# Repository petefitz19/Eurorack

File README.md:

# Eurorack
Collection of Eurorack Module Hardware and Software

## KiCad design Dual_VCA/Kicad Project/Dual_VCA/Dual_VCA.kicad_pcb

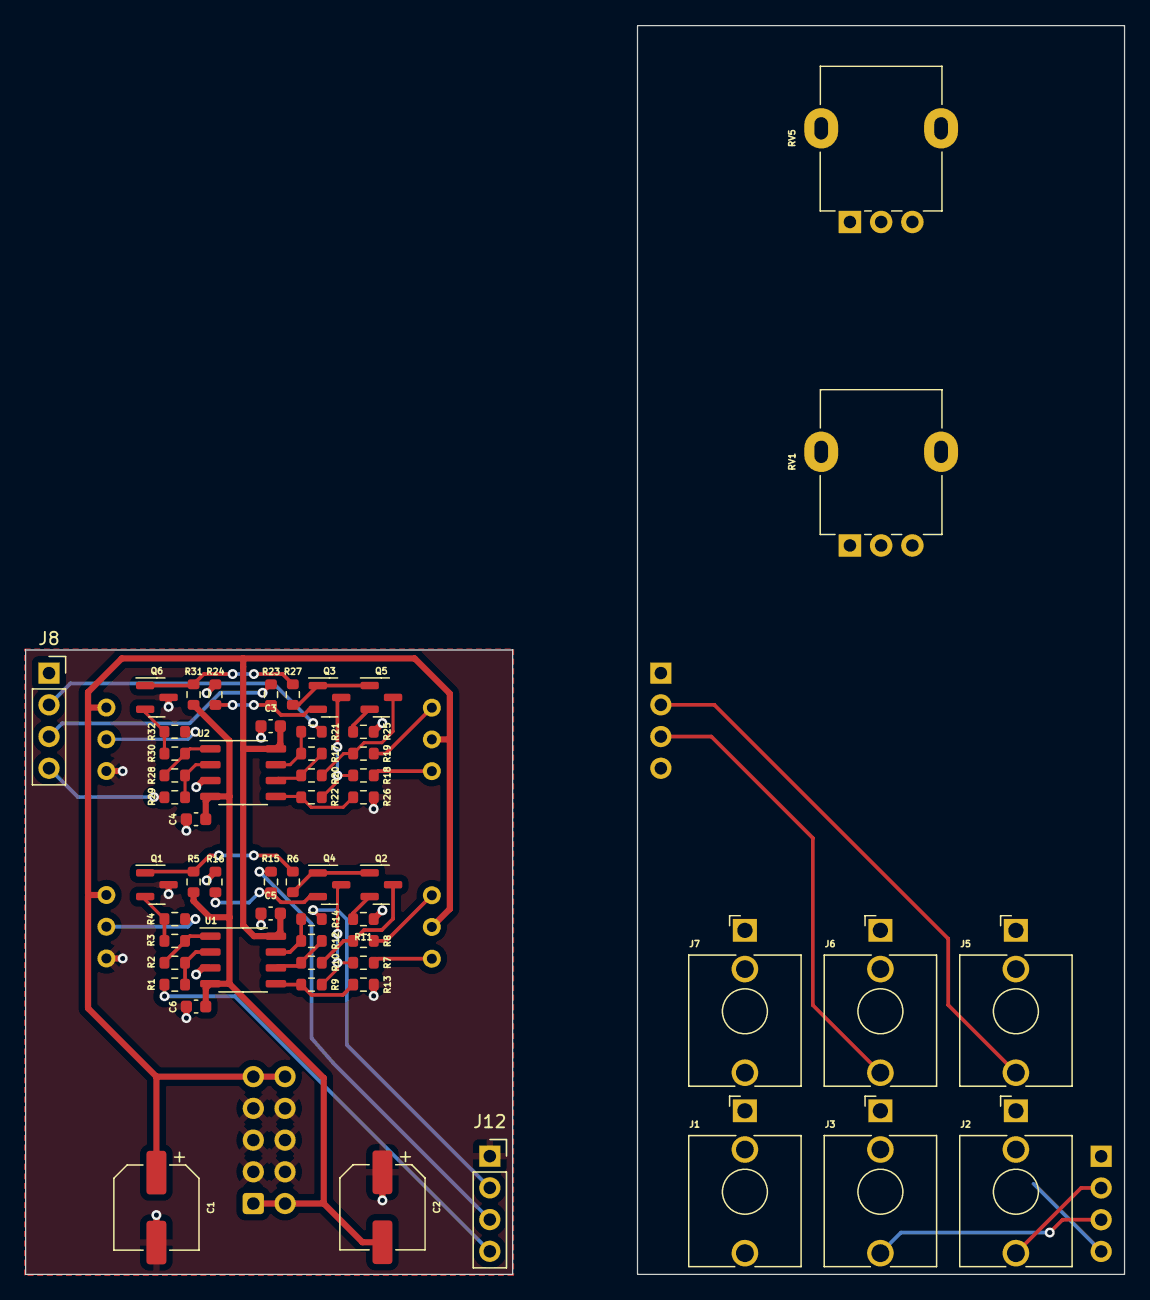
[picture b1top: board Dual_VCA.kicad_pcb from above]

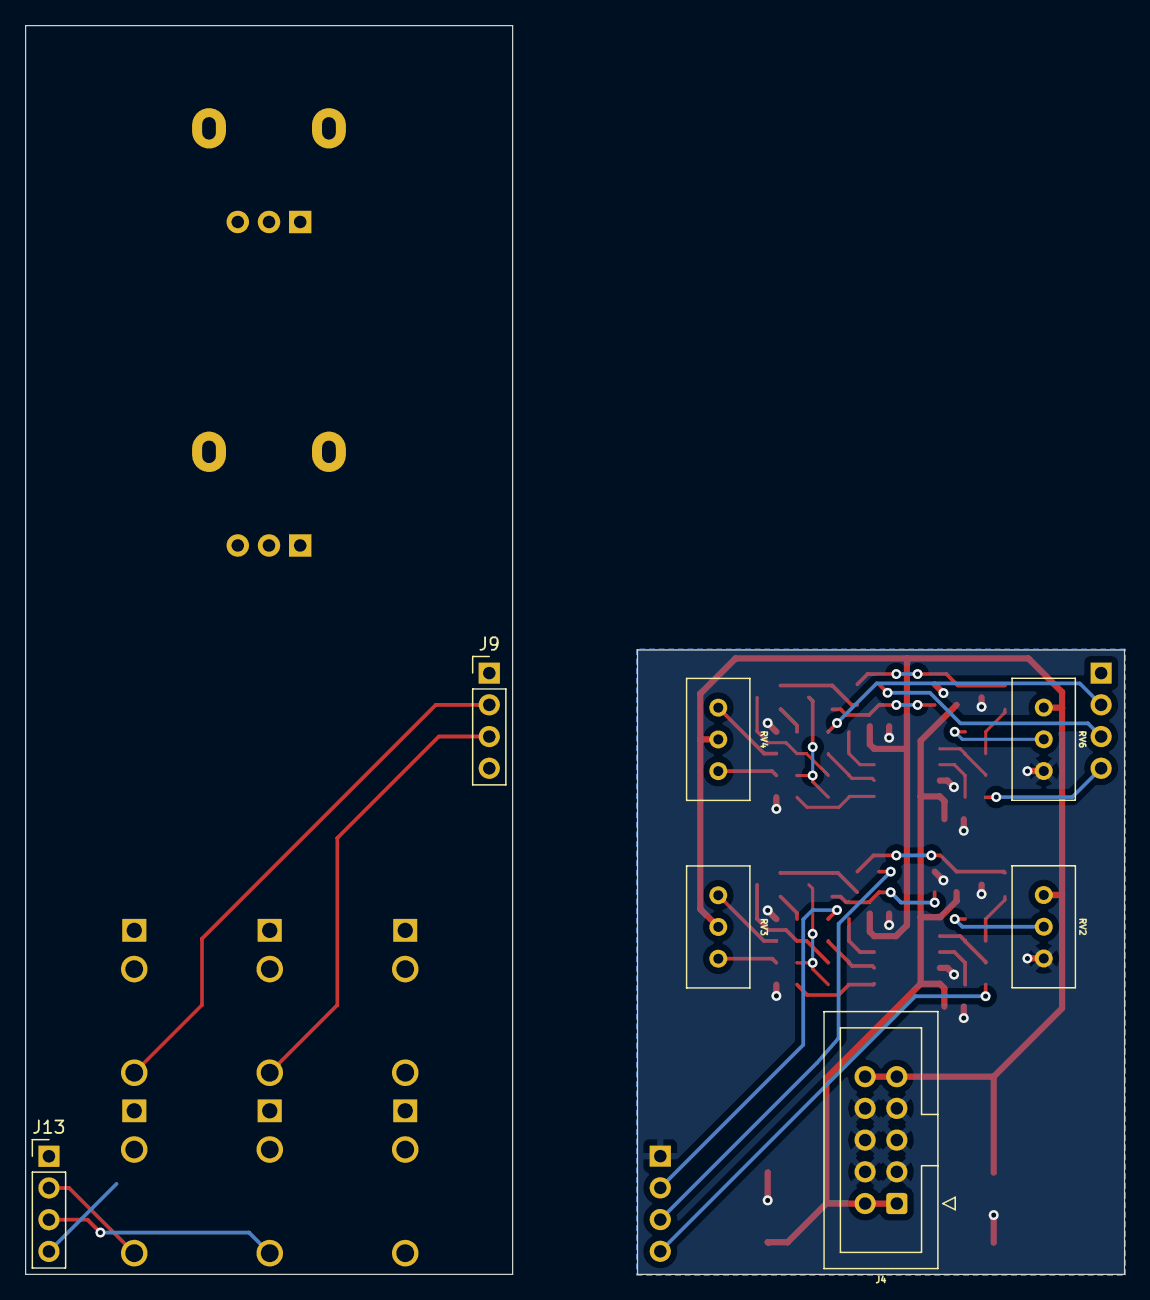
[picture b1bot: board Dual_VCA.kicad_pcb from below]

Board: 2 copper layers, 88.0 x 100.0 mm, 63 parts (7 on the bottom side), 47 nets.

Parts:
C1, C2: 10uF; CP_Elec_6.3x5.4
C3, C4, C5, C6: 100nF; C_0603_1608Metric
J1, J7: CV_IN; Jack_3.5mm_QingPu_WQP-PJ398SM_Vertical_CircularHoles
J2, J5: AUDIO_OUT; Jack_3.5mm_QingPu_WQP-PJ398SM_Vertical_CircularHoles
J3, J6: AUDIO_IN; Jack_3.5mm_QingPu_WQP-PJ398SM_Vertical_CircularHoles
J4: PWR; IDC-Header_2x05_P2.54mm_Vertical
J8: Conn_2A; PinSocket_1x04_P2.54mm_Vertical
J9: Conn_2B; PinHeader_1x04_P2.54mm_Vertical
J12: Conn_1A; PinSocket_1x04_P2.54mm_Vertical
J13: Conn_1B; PinHeader_1x04_P2.54mm_Vertical
Q1, Q2, Q3, Q4, Q5, Q6: 2N3904; SOT-23
R1, R2, R28, R29: 100k; R_0603_1608Metric
R3, R4, R5, R30, R31, R32: 10k; R_0603_1608Metric
R6, R27: 33k; R_0603_1608Metric
R7, R8, R9, R10, R18, R19, R20, R22: 15k; R_0603_1608Metric
R11, R14, R16, R21, R24, R25: 1K; R_0603_1608Metric
R12, R13, R17, R26: 150k; R_0603_1608Metric
R15, R23: 200k; R_0603_1608Metric
RV1, RV5: 100k; Potentiometer_Alpha_RD901F-40-00D_Single_Vertical
RV2, RV6: 10k; Potentiometer_Bourns_3296W_Vertical
RV3, RV4: 5k; Potentiometer_Bourns_3296W_Vertical
U1, U2: TL072; SOP-8_3.9x4.9mm_P1.27mm

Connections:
+12V: C1.1, C3.2, C5.2, J4.9, J4.10, RV2.3, RV3.2, RV4.2, RV6.3, U1.8 (V+), U2.8 (V+)
-12V: C2.2, C4.2, C6.2, J4.1, J4.2, R5.2, R31.2, U1.4 (V-), U2.4 (V-)
/cv1_a: J12.4, R1.2
/cv1_b: J13.4, RV1.2
/cv2_a: J8.4, R29.2
/cv2_b: J9.4, RV5.2
/in1_a: J12.3, R15.1
/in1_b: J3.T, J13.3
/in2_a: J8.3, R23.1
/in2_b: J6.T, J9.3
/out1_a: J12.2, R14.1
/out1_b: J2.T, J13.2
/out2_a: J8.2, R21.1
/out2_b: J5.T, J9.2
GND: C1.2, C2.1, C3.1, C4.1, C5.1, C6.1, J1.S, J2.S, J3.S, J4.3, J4.4, J4.5, J4.6, J4.7, J4.8, J5.S, J6.S, J7.S, J12.1, J13.1, Q1.3 (C), Q6.3 (C), R11.1, R13.1, R16.1, R24.1, R25.1, R26.1, RV1.1, RV2.1, RV5.1, RV6.1, U1.3 (+), U2.3 (+)
unnamed: J1.T, RV1.3
unnamed: J7.T, RV5.3
unnamed: Q1.2 (B), R3.1, R4.1
unnamed: Q1.1 (E), R5.1, R6.2
unnamed: Q2.2 (B), R11.2
unnamed: Q2.3 (C), R8.2, R10.1
unnamed: Q2.1 (E), Q4.1 (E), R6.1
unnamed: Q3.2 (B), R23.2, R24.2
unnamed: Q3.3 (C), R18.2, R22.1
unnamed: Q3.1 (E), Q5.1 (E), R27.1
unnamed: Q4.2 (B), R15.2, R16.2
unnamed: Q4.3 (C), R7.2, R9.1
unnamed: Q5.2 (B), R25.2
unnamed: Q5.3 (C), R19.2, R20.1
unnamed: Q6.2 (B), R30.1, R32.1
unnamed: Q6.1 (E), R27.2, R31.1
unnamed: R2.1, R3.2, U1.1
unnamed: R4.2, RV2.2
unnamed: R7.1, RV3.1
unnamed: R8.1, RV3.3
unnamed: R12.2, R14.2, U1.7
unnamed: R17.2, R21.2, U2.7
unnamed: R18.1, RV4.1
unnamed: R19.1, RV4.3
unnamed: R28.1, R30.2, U2.1
unnamed: R32.2, RV6.2
unnamed: R1.1, R2.2, U1.2 (-)
unnamed: R9.2, R13.2, U1.5 (+)
unnamed: R10.2, R12.1, U1.6 (-)
unnamed: R28.2, R29.1, U2.2 (-)
unnamed: R22.2, R26.2, U2.5 (+)
unnamed: R17.1, R20.2, U2.6 (-)

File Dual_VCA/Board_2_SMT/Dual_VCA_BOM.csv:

Comment,Designator,Footprint,LCSC Part Number
10uF,"C1,C2",CP_Elec_6.3x5.4,C5221839
100nF Unpolarized capacitor,"C3,C4,C5,C6",C_0603_1608Metric,C1591
"2N3904 0.2A Ic, 40V Vce, Small Signal NPN Transistor, TO-92","Q1,Q2,Q3,Q4,Q5,Q6",SOT-23,C18536
100k Resistor,"R1,R2,R28,R29",R_0603_1608Metric,C25803
10k Resistor,"R3,R4,R5,R30,R31,R32",R_0603_1608Metric,C25804
33k Resistor,"R6,R27",R_0603_1608Metric,C4216
15k Resistor,"R7,R8,R9,R10,R18,R19,R20,R22",R_0603_1608Metric,C22809
1K Resistor,"R11,R14,R16,R21,R24,R25",R_0603_1608Metric,C21190
150k Resistor,"R12,R13,R17,R26",R_0603_1608Metric,C22807
200k Resistor,"R15,R23",R_0603_1608Metric,C25811
"TL072 Dual Low-Noise JFET-Input Operational Amplifiers, DIP-8/SOIC-8","U1,U2",SOP-8_3.9x4.9mm_P1.27mm,C67473

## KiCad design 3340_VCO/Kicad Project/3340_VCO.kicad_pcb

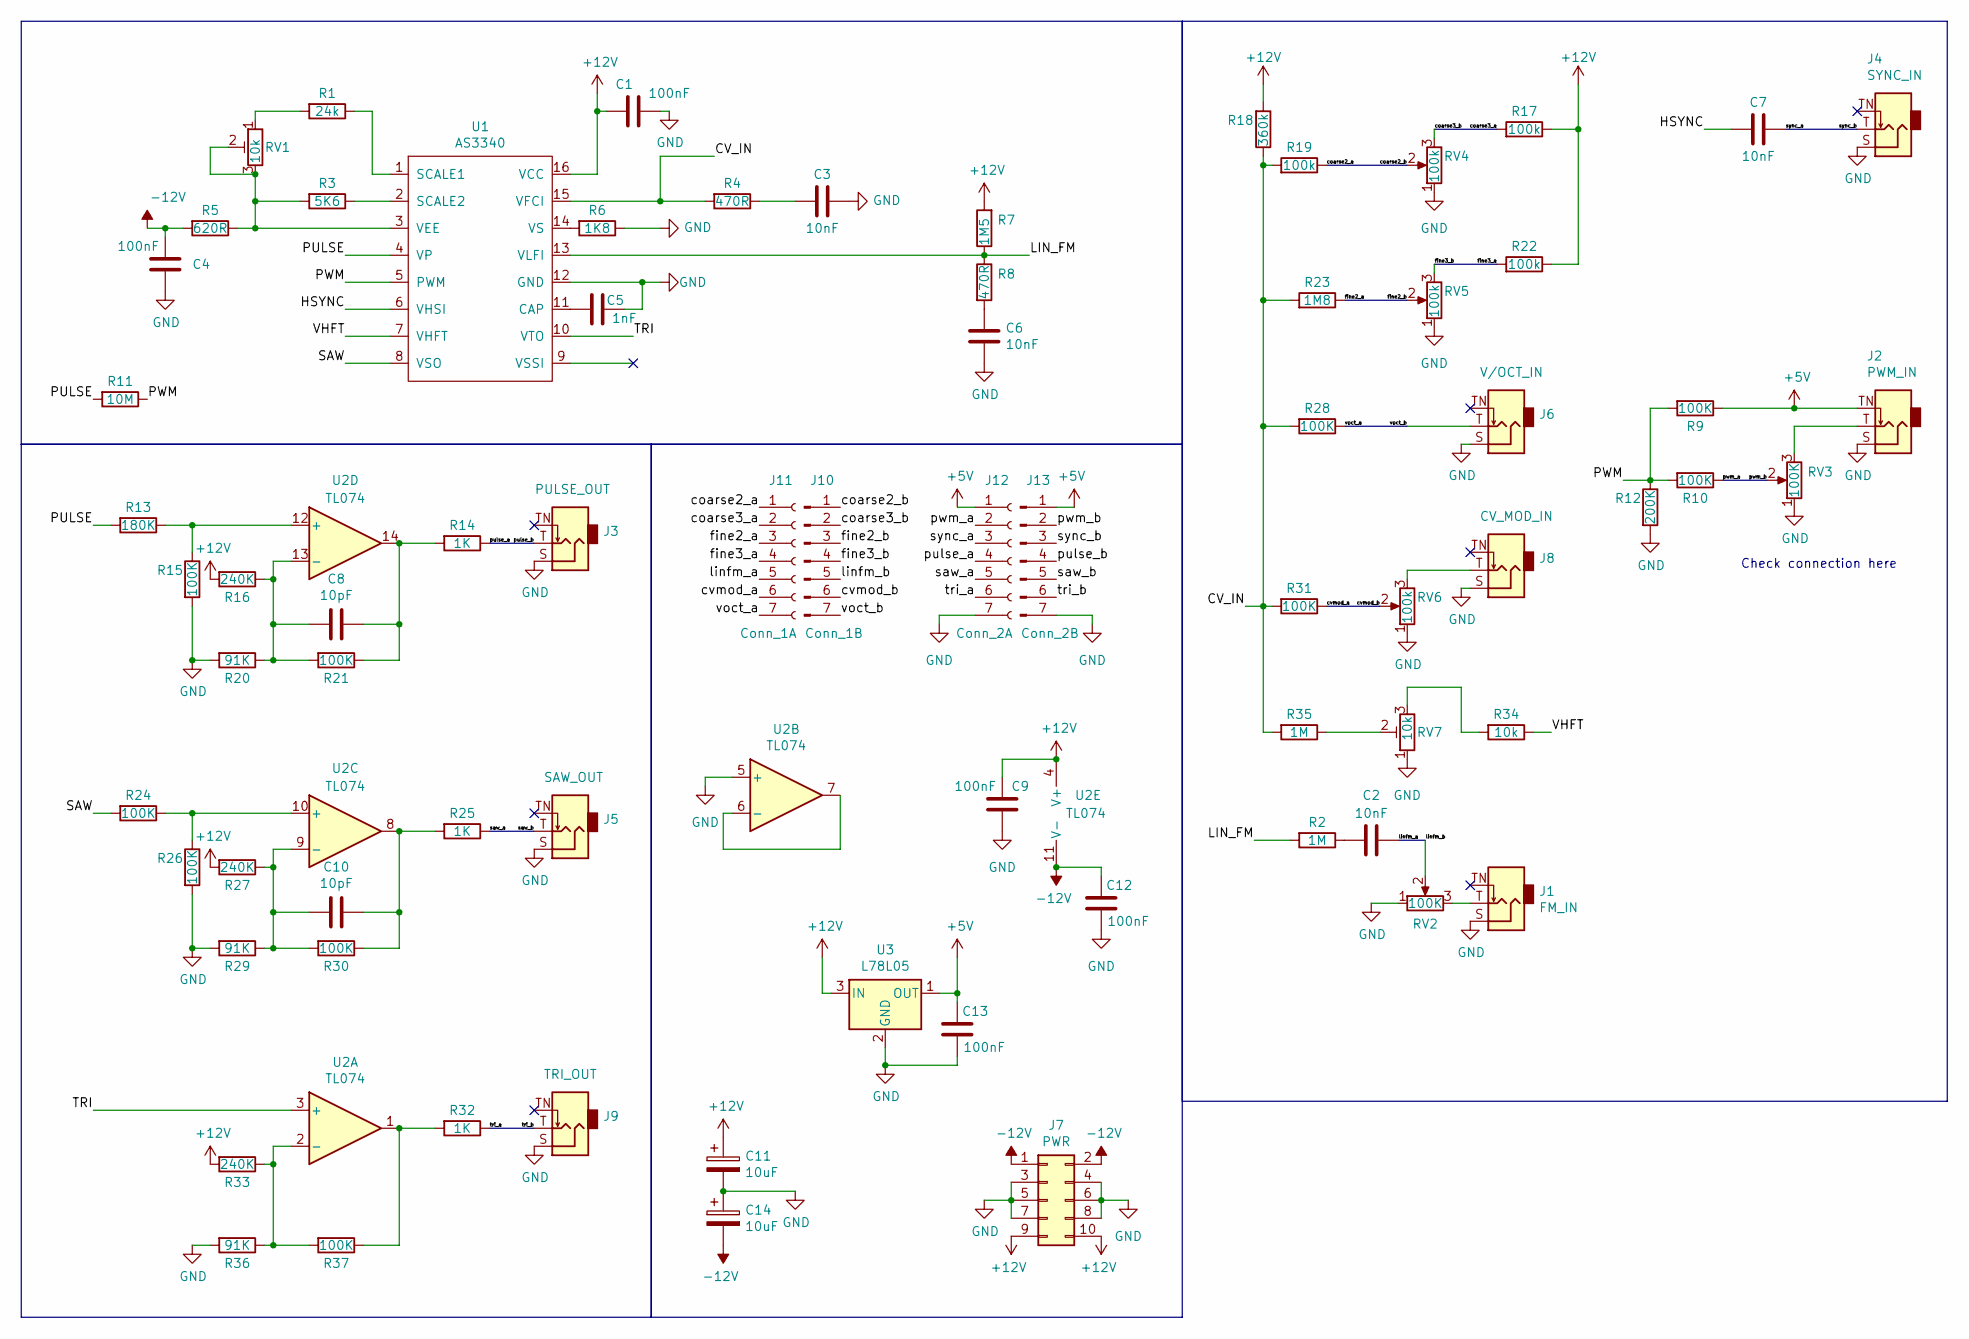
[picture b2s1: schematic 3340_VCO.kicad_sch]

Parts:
C1, C4, C9, C12, C13: 100nF; C_0603_1608Metric; LCSC C1591
C2, C3, C6, C7: 10nF; C_0603_1608Metric; LCSC C100042
C5: 1nF; C_0603_1608Metric; LCSC C178413
C8, C10: 10pF; C_0603_1608Metric; LCSC C91367
C11, C14: 10uF; CP_Elec_6.3x5.4; LCSC C5221839
J1: FM_IN; Jack_3.5mm_QingPu_WQP-PJ398SM_Vertical_CircularHoles
J2: PWM_IN; Jack_3.5mm_QingPu_WQP-PJ398SM_Vertical_CircularHoles
J3: PULSE_OUT; Jack_3.5mm_QingPu_WQP-PJ398SM_Vertical_CircularHoles
J4: SYNC_IN; Jack_3.5mm_QingPu_WQP-PJ398SM_Vertical_CircularHoles
J5: SAW_OUT; Jack_3.5mm_QingPu_WQP-PJ398SM_Vertical_CircularHoles
J6: V/OCT_IN; Jack_3.5mm_QingPu_WQP-PJ398SM_Vertical_CircularHoles
J7: PWR; IDC-Header_2x05_P2.54mm_Vertical
J8: CV_MOD_IN; Jack_3.5mm_QingPu_WQP-PJ398SM_Vertical_CircularHoles
J9: TRI_OUT; Jack_3.5mm_QingPu_WQP-PJ398SM_Vertical_CircularHoles
J10: Conn_1A; PinSocket_1x07_P2.54mm_Vertical
J11: Conn_1B; PinHeader_1x07_P2.54mm_Vertical
J12: Conn_2B; PinHeader_1x07_P2.54mm_Vertical
J13: Conn_2A; PinSocket_1x07_P2.54mm_Vertical
R1: 24k; R_0603_1608Metric; LCSC C23352
R2, R35: 1M; R_0603_1608Metric; LCSC C22935
R3: 5K6; R_0603_1608Metric; LCSC C23189
R4, R8: 470R; R_0603_1608Metric; LCSC C23179
R5: 620R; R_0603_1608Metric; LCSC C23220
R6: 1K8; R_0603_1608Metric; LCSC C4177
R7: 1M5; R_0603_1608Metric; LCSC C4172
R9, R10, R15, R21, R24, R26, R28, R30, R31, R37: 100K; R_0603_1608Metric; LCSC C25803
R11: 10M; R_0603_1608Metric; LCSC C7250
R12: 200K; R_0603_1608Metric; LCSC C25811
R13: 180K; R_0603_1608Metric; LCSC C22827
R14, R25, R32: 1K; R_0603_1608Metric; LCSC C21190
R16, R27, R33: 240K; R_0603_1608Metric; LCSC C4197
R17, R22: 100k; R_0603_1608Metric; LCSC C25803
R18: 360k; R_0603_1608Metric; LCSC C23146
R19: 100k; R_0603_1608Metric
R20, R29, R36: 91K; R_0603_1608Metric; LCSC C23265
R23: 1M8; R_0603_1608Metric; LCSC C13318
R34: 10k; R_0603_1608Metric; LCSC C25804
RV1, RV7: 10k; Potentiometer_Bourns_3296W_Vertical
RV2, RV3: 100K; Potentiometer_Alpha_RD901F-40-00D_Single_Vertical
RV4, RV5, RV6: 100k; Potentiometer_Alpha_RD901F-40-00D_Single_Vertical
U1: AS3340; DIP-16_W10.16mm_LongPads
U2: TL074; SOIC-14_3.9x8.7mm_P1.27mm; LCSC C12594
U3: L78L05; SOT-89-3; LCSC C3025155

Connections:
+5V: C13.2, J2.TN, J12.1, J13.1, R9.1, U3.1 (OUT)
+12V: C1.2, C9.2, C11.1, J7.9, J7.10, R7.2, R16.2, R17.1, R18.2, R22.1, R27.2, R33.2, U1.16 (VCC), U2.4 (V+), U3.3 (IN)
-12V: C4.2, C12.2, C14.2, J7.1, J7.2, R5.2, U2.11 (V-)
/CV_IN: R4.2, R18.1, R19.2, R23.2, R28.2, R31.2, R35.2, U1.15 (VFCI)
/HSYNC: C7.2, U1.6 (VHSI)
/LIN_FM: R2.2, R7.1, R8.1, U1.13 (VLFI)
/PULSE: R11.2, R13.2, U1.4 (VP)
/PWM: R9.2, R10.2, R11.1, R12.1, U1.5 (PWM)
/SAW: R24.2, U1.8 (VSO)
/TRI: U1.10 (VTO), U2.3 (+)
/VHFT: R34.1, U1.7 (VHFT)
/coarse2_a: J11.1, R19.1
/coarse2_b: J10.1, RV4.2
/coarse3_a: J11.2, R17.2
/coarse3_b: J10.2, RV4.3
/cvmod_a: J11.6, R31.1
/cvmod_b: J10.6, RV6.2
/fine2_a: J11.3, R23.1
/fine2_b: J10.3, RV5.2
/fine3_a: J11.4, R22.2
/fine3_b: J10.4, RV5.3
/linfm_a: C2.1, J11.5
/linfm_b: J10.5, RV2.2
/pulse_a: J12.4, R14.1
/pulse_b: J3.T, J13.4
/pwm_a: J12.2, R10.1
/pwm_b: J13.2, RV3.2
/saw_a: J12.5, R25.1
/saw_b: J5.T, J13.5
/sync_a: C7.1, J12.3
/sync_b: J4.T, J13.3
/tri_a: J12.6, R32.1
/tri_b: J9.T, J13.6
/voct_a: J11.7, R28.1
/voct_b: J6.T, J10.7
GND: C1.1, C3.1, C4.1, C5.1, C6.2, C9.1, C11.2, C12.1, C13.1, C14.1, J1.S, J2.S, J3.S, J4.S, J5.S, J6.S, J7.3, J7.4, J7.5, J7.6, J7.7, J7.8, J8.S, J9.S, J12.7, J13.7, R6.1, R12.2, R15.2, R20.2, R26.2, R29.2, R36.2, RV2.1, RV3.1, RV4.1, RV5.1, RV6.1, RV7.1, U1.12 (GND), U2.5 (+), U3.2 (GND)
unnamed: C2.2, R2.1
unnamed: C3.2, R4.1
unnamed: C6.1, R8.2
unnamed: C8.1, R14.2, R21.1, U2.14
unnamed: C10.1, R25.2, R30.1, U2.8
unnamed: J1.T, RV2.3
unnamed: J2.T, RV3.3
unnamed: J8.T, RV6.3
unnamed: R1.2, RV1.1
unnamed: R32.2, R37.1, U2.1
unnamed: R34.2, RV7.3
unnamed: R35.1, RV7.2
unnamed: C5.2, U1.11 (CAP)
unnamed: R1.1, U1.1 (SCALE1)
unnamed: R3.1, U1.2 (SCALE2)
unnamed: R3.2, R5.1, RV1.2, RV1.3, U1.3 (VEE)
unnamed: R6.2, U1.14 (VS)
unnamed: R33.1, R36.1, R37.2, U2.2 (-)
unnamed: U2.6 (-), U2.7
unnamed: R24.1, R26.1, U2.10 (+)
unnamed: C10.2, R27.1, R29.1, R30.2, U2.9 (-)
unnamed: R13.1, R15.1, U2.12 (+)
unnamed: C8.2, R16.1, R20.1, R21.2, U2.13 (-)

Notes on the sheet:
Check connection here

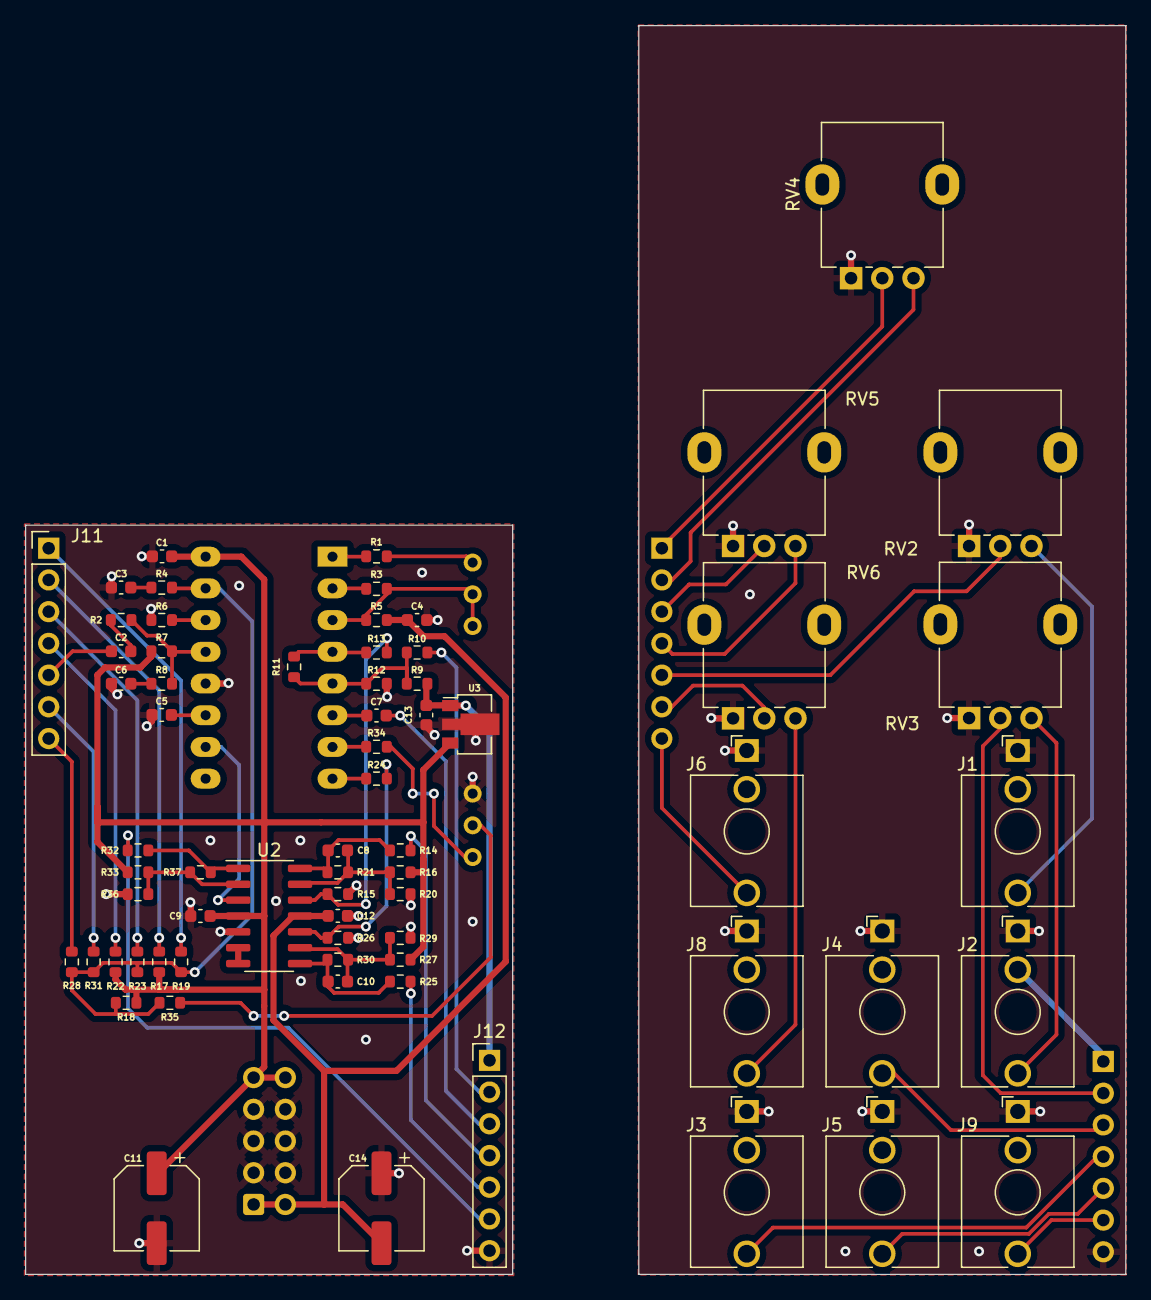
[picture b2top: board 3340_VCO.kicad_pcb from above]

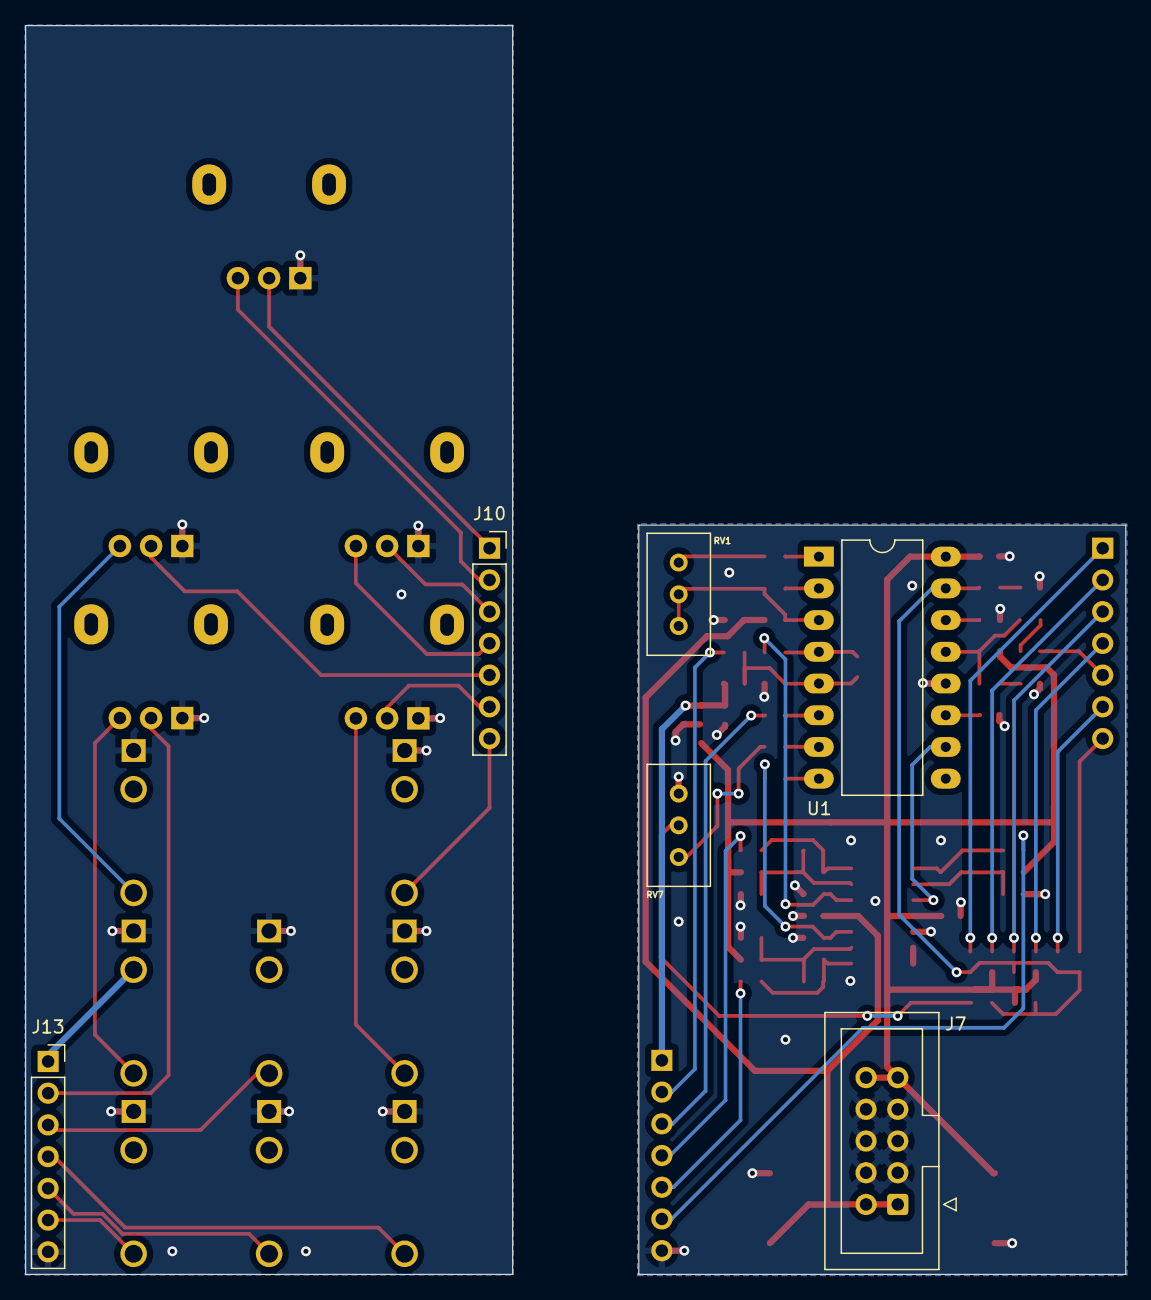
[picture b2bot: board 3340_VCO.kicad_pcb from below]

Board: 2 copper layers, 88.1 x 100.0 mm, 74 parts (6 on the bottom side), 59 nets.

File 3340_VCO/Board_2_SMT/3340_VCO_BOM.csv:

Comment,Designator,Footprint,LCSC Part Number
100nF,"C1,C4,C9,C12,C13",Capacitor_SMD:C_0603_1608Metric,C1591
10uF,"C11,C14",Capacitor_SMD:CP_Elec_6.3x5.4,C5221839
10nF,"C2,C3,C6,C7",Capacitor_SMD:C_0603_1608Metric,C100042
1nF,C5,Capacitor_SMD:C_0603_1608Metric,C178413
10pF,"C8,C10",Capacitor_SMD:C_0603_1608Metric,C91367
24k,R1,Resistor_SMD:R_0603_1608Metric,C23352
10M,R11,Resistor_SMD:R_0603_1608Metric,C7250
200K,R12,Resistor_SMD:R_0603_1608Metric,C25811
180K,R13,Resistor_SMD:R_0603_1608Metric,C22827
1K,"R14,R25,R32",Resistor_SMD:R_0603_1608Metric,C21190
240K,"R16,R27,R33",Resistor_SMD:R_0603_1608Metric,C4197
100k,"R17,R19,R22",Resistor_SMD:R_0603_1608Metric,C25803
360k,R18,Resistor_SMD:R_0603_1608Metric,C23146
1M,"R2,R35",Resistor_SMD:R_0603_1608Metric,C22935
91K,"R20,R29,R36",Resistor_SMD:R_0603_1608Metric,C23265
1M8,R23,Resistor_SMD:R_0603_1608Metric,C13318
5K6,R3,Resistor_SMD:R_0603_1608Metric,C23189
10k,R34,Resistor_SMD:R_0603_1608Metric,C25804
470R,"R4,R8",Resistor_SMD:R_0603_1608Metric,C23179
620R,R5,Resistor_SMD:R_0603_1608Metric,C23220
1K8,R6,Resistor_SMD:R_0603_1608Metric,C4177
1M5,R7,Resistor_SMD:R_0603_1608Metric,C4172
100K,"R9,R10,R15,R21,R24,R26,R28,R30,R31,R37",Resistor_SMD:R_0603_1608Metric,C25803
TL074,U2,Package_SO:SOIC-14_3.9x8.7mm_P1.27mm,C12594
L78L05,U3,Package_TO_SOT_SMD:SOT-89-3,C3025155

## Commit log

2023-10-11 Added Proj Files for CEM3340 VCO
2023-10-14 Adding Dual VCA. Still need to improve daughter board pin mapping
2024-01-04 Recent updates for eurorack pcbs
2024-01-22 Updating project files
2024-03-08 Generate JLCPCB files for VCO and VCA
2024-03-08 Accounted for NPN transistor pinout being wrong in REV 1
